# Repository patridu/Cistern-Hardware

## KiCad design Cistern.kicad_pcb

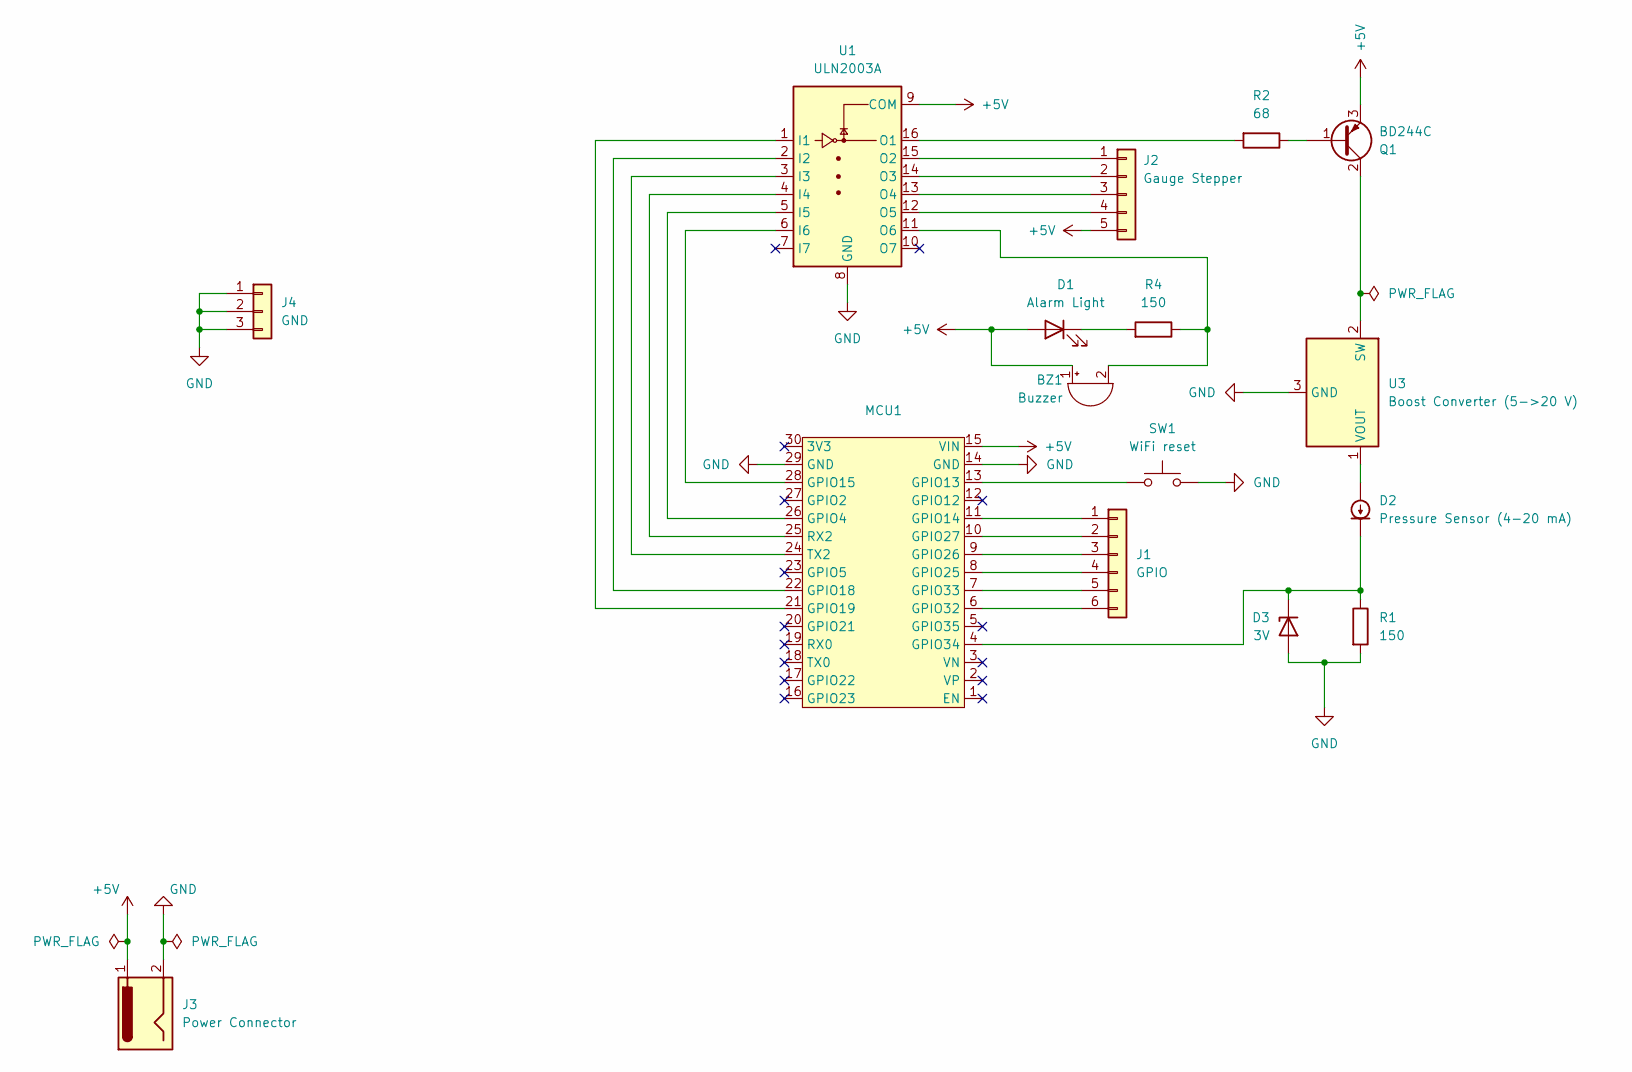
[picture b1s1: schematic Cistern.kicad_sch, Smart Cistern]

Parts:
BZ1: Buzzer; AZDelivery_KY-012_Buzzer
D1: Alarm Light; LED_D5.0mm
D2: Pressure Sensor (4-20 mA); PinHeader_1x02_P2.54mm_Vertical
D3: 3V; D_A-405_P7.62mm_Horizontal
J1: GPIO; PinHeader_1x06_P2.54mm_Vertical
J2: Gauge Stepper; JST_XH_B5B-XH-A_1x05_P2.54mm_Vertical
J3: Power Connector; TerminalBlock_bornier-2_P5.08mm
J4: GND; PinHeader_1x03_P2.54mm_Vertical
MCU1: ESP32-NodeMCU
Q1: BD244C; TO-220-3_Vertical
R1, R4: 150; R_Axial_DIN0207_L6.3mm_D2.5mm_P7.62mm_Horizontal
R2: 68; R_Axial_DIN0207_L6.3mm_D2.5mm_P7.62mm_Horizontal
SW1: WiFi reset; SW_PUSH_6mm
U1: ULN2003A; DIP-16_W7.62mm_Socket
U3: Boost Converter (5->20 V); DC-DC_Module_XL6009E1

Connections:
+5V: BZ1.1 (+), D1.2 (A), J2.5, J3.1, MCU1.15 (VIN), Q1.3 (E), U1.9 (COM)
GND: D3.2 (A), J3.2, J4.1, J4.2, J4.3, MCU1.14 (GND), MCU1.29 (GND), R1.2, SW1.2, U1.8 (GND), U3.3 (GND)
unnamed: BZ1.2 (-), R4.1, U1.11 (O6)
unnamed: D1.1 (K), R4.2
unnamed: D2.2 (A), U3.1 (VOUT)
unnamed: D2.1 (K), D3.1 (K), MCU1.4 (GPIO34), R1.1
unnamed: J1.1, MCU1.11 (GPIO14)
unnamed: J1.2, MCU1.10 (GPIO27)
unnamed: J1.3, MCU1.9 (GPIO26)
unnamed: J1.4, MCU1.8 (GPIO25)
unnamed: J1.5, MCU1.7 (GPIO33)
unnamed: J1.6, MCU1.6 (GPIO32)
unnamed: J2.1, U1.15 (O2)
unnamed: J2.2, U1.14 (O3)
unnamed: J2.3, U1.13 (O4)
unnamed: J2.4, U1.12 (O5)
unnamed: MCU1.26 (GPIO4), U1.5 (I5)
unnamed: MCU1.13 (GPIO13), SW1.1
unnamed: MCU1.28 (GPIO15), U1.6 (I6)
unnamed: MCU1.22 (GPIO18), U1.2 (I2)
unnamed: MCU1.21 (GPIO19), U1.1 (I1)
unnamed: MCU1.25 (RX2), U1.4 (I4)
unnamed: MCU1.24 (TX2), U1.3 (I3)
unnamed: Q1.1 (B), R2.1
unnamed: Q1.2 (C), U3.2 (SW)
unnamed: R2.2, U1.16 (O1)

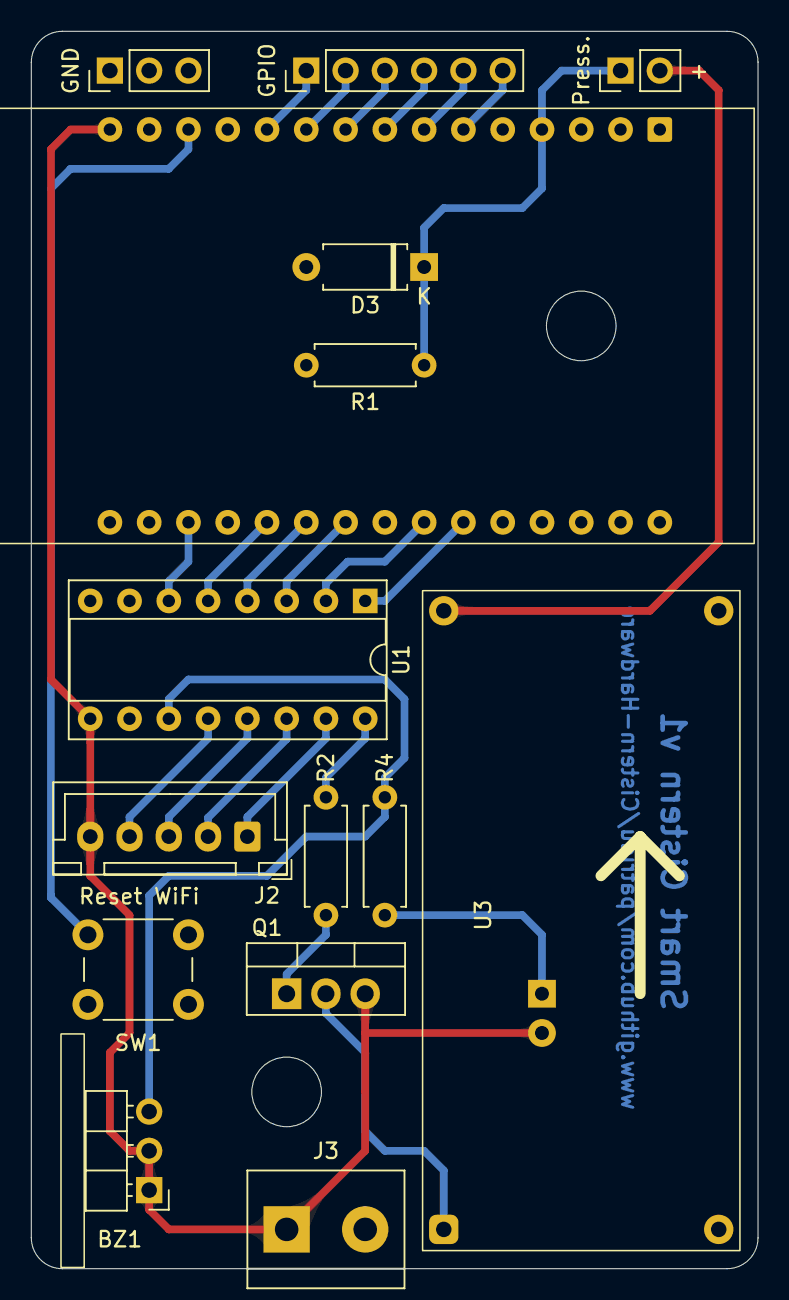
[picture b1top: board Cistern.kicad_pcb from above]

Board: 2 copper layers, 47.0 x 80.0 mm, 18 parts (1 on the bottom side), 26 nets.

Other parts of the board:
NPTH: MountingHole_4.5mm
NPTH#2: MountingHole_4.5mm

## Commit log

2024-08-10 Changing schematic to fit parts and starting PCB design
2024-08-11 Working on board layout
2024-08-11 Finishing hole-grid ready PCB design
2024-08-11 Small improvement to buzzer clearance
2024-08-25 Changing pin assignments to make things work
2024-08-25 Changing assignments some more and updating board design
2024-08-25 Adding gauge calibration sensor
2024-08-25 Changing pin assignments some more, adding gauge calibration sensor
2024-12-23 Updating gitignore
2024-12-23 Rebasing project on AISLER's design rules
2024-12-24 Starting PCB layout
2024-12-24 Finishing first version of board layout
2024-12-24 Minor improvements, ensuring design rules
2024-12-25 Improving design some more, fixing custom footprints
2024-12-28 Adding teardrops
2024-12-28 Replacing individual pins with GPIO header
2024-12-28 Adding GND header
2024-12-28 Rounding corners, improving GND plane and buzzer placement
2024-12-29 Fine-tuning LED position
